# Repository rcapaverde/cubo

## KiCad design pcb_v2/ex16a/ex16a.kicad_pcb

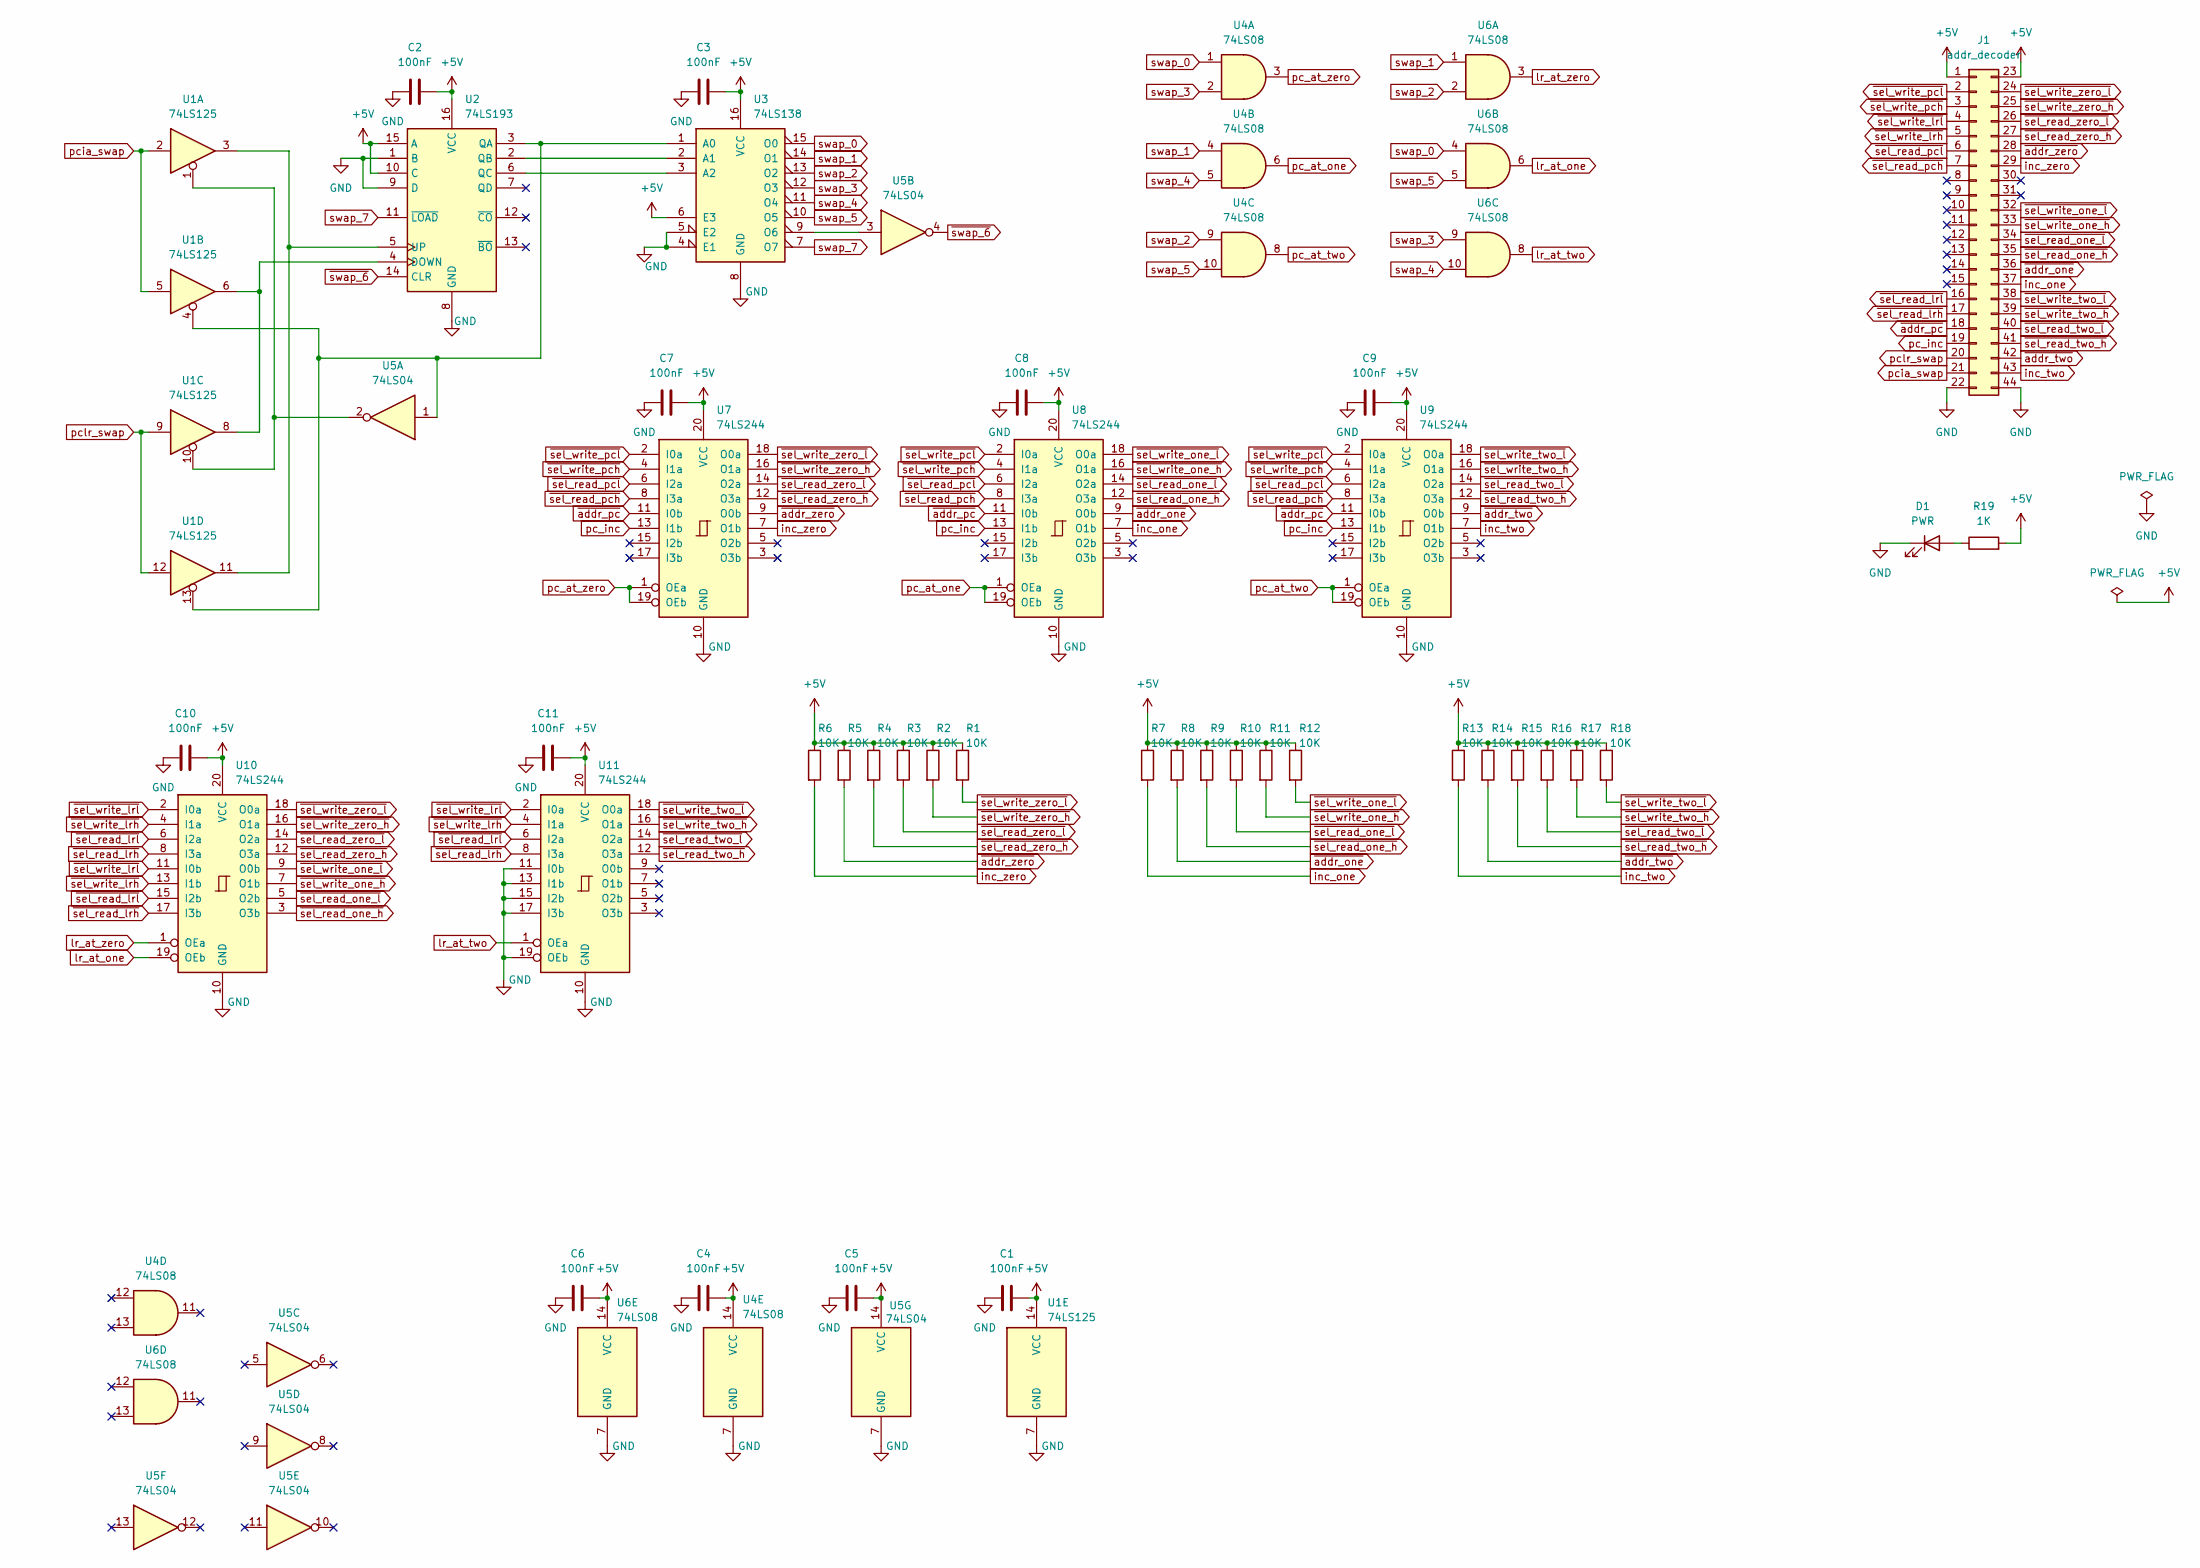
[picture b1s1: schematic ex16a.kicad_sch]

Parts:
C1, C2, C3, C4, C5, C6, C7, C8, C9, C10, C11: 100nF; C_Disc_D5.1mm_W3.2mm_P5.00mm
D1: PWR; LED_D5.0mm
J1: addr_decoder; edge-connector-44
R1, R2, R3, R4, R5, R6, R7, R8, R9, R10, R11, R12, R13, R14, R15, R16, R17, R18: 10K; R_Axial_DIN0207_L6.3mm_D2.5mm_P7.62mm_Horizontal
R19: 1K; R_Axial_DIN0207_L6.3mm_D2.5mm_P7.62mm_Horizontal
U1: 74LS125; DIP-14_W7.62mm
U2: 74LS193; DIP-16_W7.62mm
U3: 74LS138; DIP-16_W7.62mm
U4, U6: 74LS08; DIP-14_W7.62mm
U5: 74LS04; DIP-14_W7.62mm
U7, U8, U9, U10, U11: 74LS244; DIP-20_W7.62mm

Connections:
+5V: C1.2, C2.2, C3.2, C4.2, C5.2, C6.2, C7.2, C8.2, C9.2, C10.2, C11.2, J1.1, J1.23, R1.1, R2.1, R3.1, R4.1, R5.1, R6.1, R7.1, R8.1, R9.1, R10.1, R11.1, R12.1, R13.1, R14.1, R15.1, R16.1, R17.1, R18.1, R19.2, U1.14 (VCC), U2.10 (C), U2.15 (A), U2.16 (VCC), U3.6 (E3), U3.16 (VCC), U4.14 (VCC), U5.14 (VCC), U6.14 (VCC), U7.20 (VCC), U8.20 (VCC), U9.20 (VCC), U10.20 (VCC), U11.20 (VCC)
GND: C1.1, C2.1, C3.1, C4.1, C5.1, C6.1, C7.1, C8.1, C9.1, C10.1, C11.1, D1.1 (K), J1.22, J1.44, U1.7 (GND), U2.1 (B), U2.8 (GND), U2.9 (D), U3.4 (E1), U3.5 (E2), U3.8 (GND), U4.7 (GND), U5.7 (GND), U6.7 (GND), U7.10 (GND), U8.10 (GND), U9.10 (GND), U10.10 (GND), U11.10 (GND), U11.11 (I0b), U11.13 (I1b), U11.15 (I2b), U11.17 (I3b), U11.19 (OEb)
unnamed: D1.2 (A), R19.1
unnamed: U1.1, U1.10, U5.2
unnamed: U1.6, U1.8, U2.4 (DOWN)
unnamed: U1.4, U1.13, U2.3 (QA), U3.1 (A0), U5.1
unnamed: U2.2 (QB), U3.2 (A1)
unnamed: U2.6 (QC), U3.3 (A2)
unnamed: U1.3, U1.11, U2.5 (UP)
unnamed: U3.9 (O6), U5.3
inc_one: J1.37, R7.2, U8.7 (O1b)
inc_two: J1.43, R13.2, U9.7 (O1b)
inc_zero: J1.29, R6.2, U7.7 (O1b)
lr_at_one: U6.6, U10.19 (OEb)
lr_at_two: U6.8, U11.1 (OEa)
lr_at_zero: U6.3, U10.1 (OEa)
pc_at_one: U4.6, U8.1 (OEa), U8.19 (OEb)
pc_at_two: U4.8, U9.1 (OEa), U9.19 (OEb)
pc_at_zero: U4.3, U7.1 (OEa), U7.19 (OEb)
pc_inc: J1.19, U7.13 (I1b), U8.13 (I1b), U9.13 (I1b)
pcia_swap: J1.21, U1.2, U1.5
pclr_swap: J1.20, U1.9, U1.12
swap_0: U3.15 (O0), U4.1, U6.4
swap_1: U3.14 (O1), U4.4, U6.1
swap_2: U3.13 (O2), U4.9, U6.2
swap_3: U3.12 (O3), U4.2, U6.9
swap_4: U3.11 (O4), U4.5, U6.10
swap_5: U3.10 (O5), U4.10, U6.5
swap_7: U2.11 (~LOAD), U3.7 (O7)
~addr_one: J1.36, R8.2, U8.9 (O0b)
~addr_pc: J1.18, U7.11 (I0b), U8.11 (I0b), U9.11 (I0b)
~addr_two: J1.42, R14.2, U9.9 (O0b)
~addr_zero: J1.28, R5.2, U7.9 (O0b)
~sel_read_lrh: J1.17, U10.8 (I3a), U10.17 (I3b), U11.8 (I3a)
~sel_read_lrl: J1.16, U10.6 (I2a), U10.15 (I2b), U11.6 (I2a)
~sel_read_one_h: J1.35, R9.2, U8.12 (O3a), U10.3 (O3b)
~sel_read_one_l: J1.34, R10.2, U8.14 (O2a), U10.5 (O2b)
~sel_read_pch: J1.7, U7.8 (I3a), U8.8 (I3a), U9.8 (I3a)
~sel_read_pcl: J1.6, U7.6 (I2a), U8.6 (I2a), U9.6 (I2a)
~sel_read_two_h: J1.41, R15.2, U9.12 (O3a), U11.12 (O3a)
~sel_read_two_l: J1.40, R16.2, U9.14 (O2a), U11.14 (O2a)
~sel_read_zero_h: J1.27, R4.2, U7.12 (O3a), U10.12 (O3a)
~sel_read_zero_l: J1.26, R3.2, U7.14 (O2a), U10.14 (O2a)
~sel_write_lrh: J1.5, U10.4 (I1a), U10.13 (I1b), U11.4 (I1a)
~sel_write_lrl: J1.4, U10.2 (I0a), U10.11 (I0b), U11.2 (I0a)
~sel_write_one_h: J1.33, R11.2, U8.16 (O1a), U10.7 (O1b)
~sel_write_one_l: J1.32, R12.2, U8.18 (O0a), U10.9 (O0b)
~sel_write_pch: J1.3, U7.4 (I1a), U8.4 (I1a), U9.4 (I1a)
~sel_write_pcl: J1.2, U7.2 (I0a), U8.2 (I0a), U9.2 (I0a)
~sel_write_two_h: J1.39, R17.2, U9.16 (O1a), U11.16 (O1a)
~sel_write_two_l: J1.38, R18.2, U9.18 (O0a), U11.18 (O0a)
~sel_write_zero_h: J1.25, R2.2, U7.16 (O1a), U10.16 (O1a)
~sel_write_zero_l: J1.24, R1.2, U7.18 (O0a), U10.18 (O0a)
~swap_6: U2.14 (CLR), U5.4

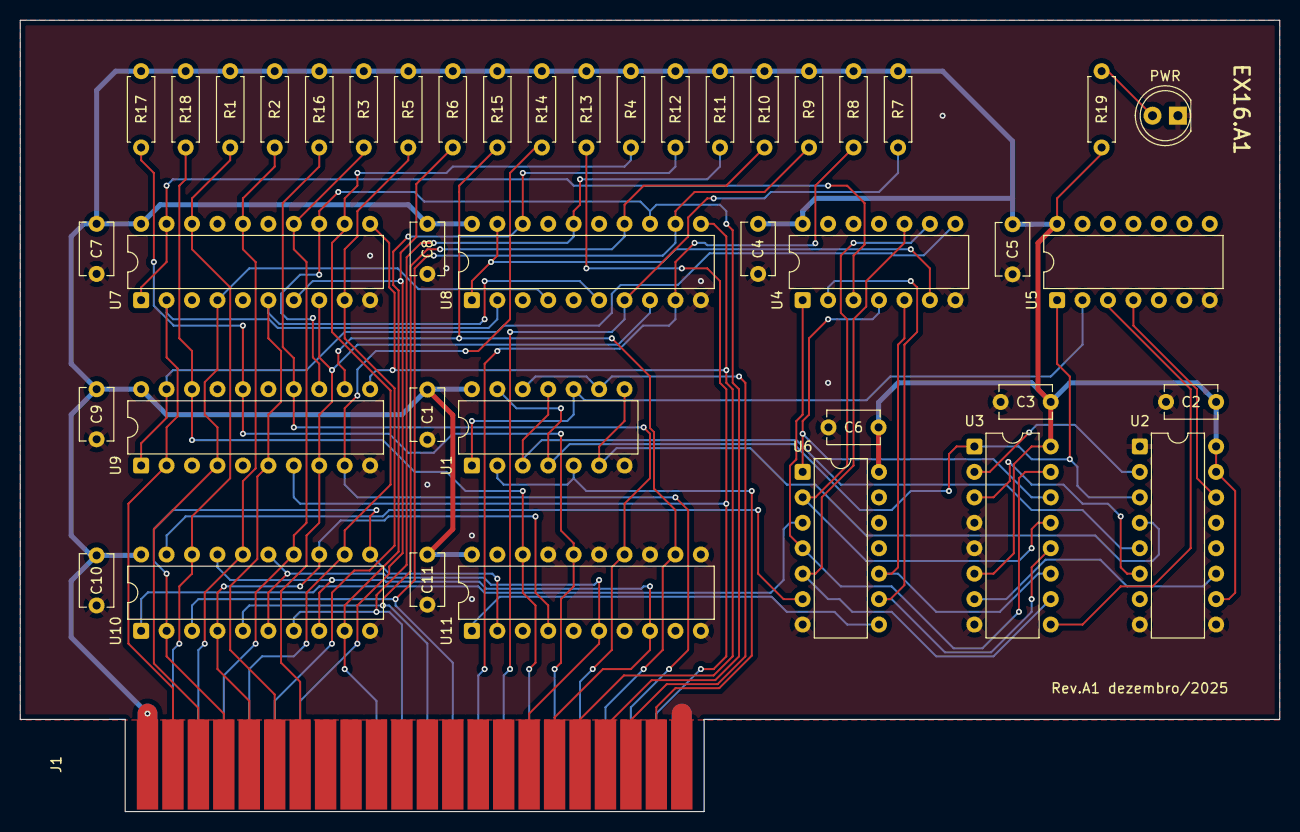
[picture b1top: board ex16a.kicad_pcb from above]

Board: 2 copper layers, 125.7 x 79.0 mm, 43 parts (0 on the bottom side), 54 nets.

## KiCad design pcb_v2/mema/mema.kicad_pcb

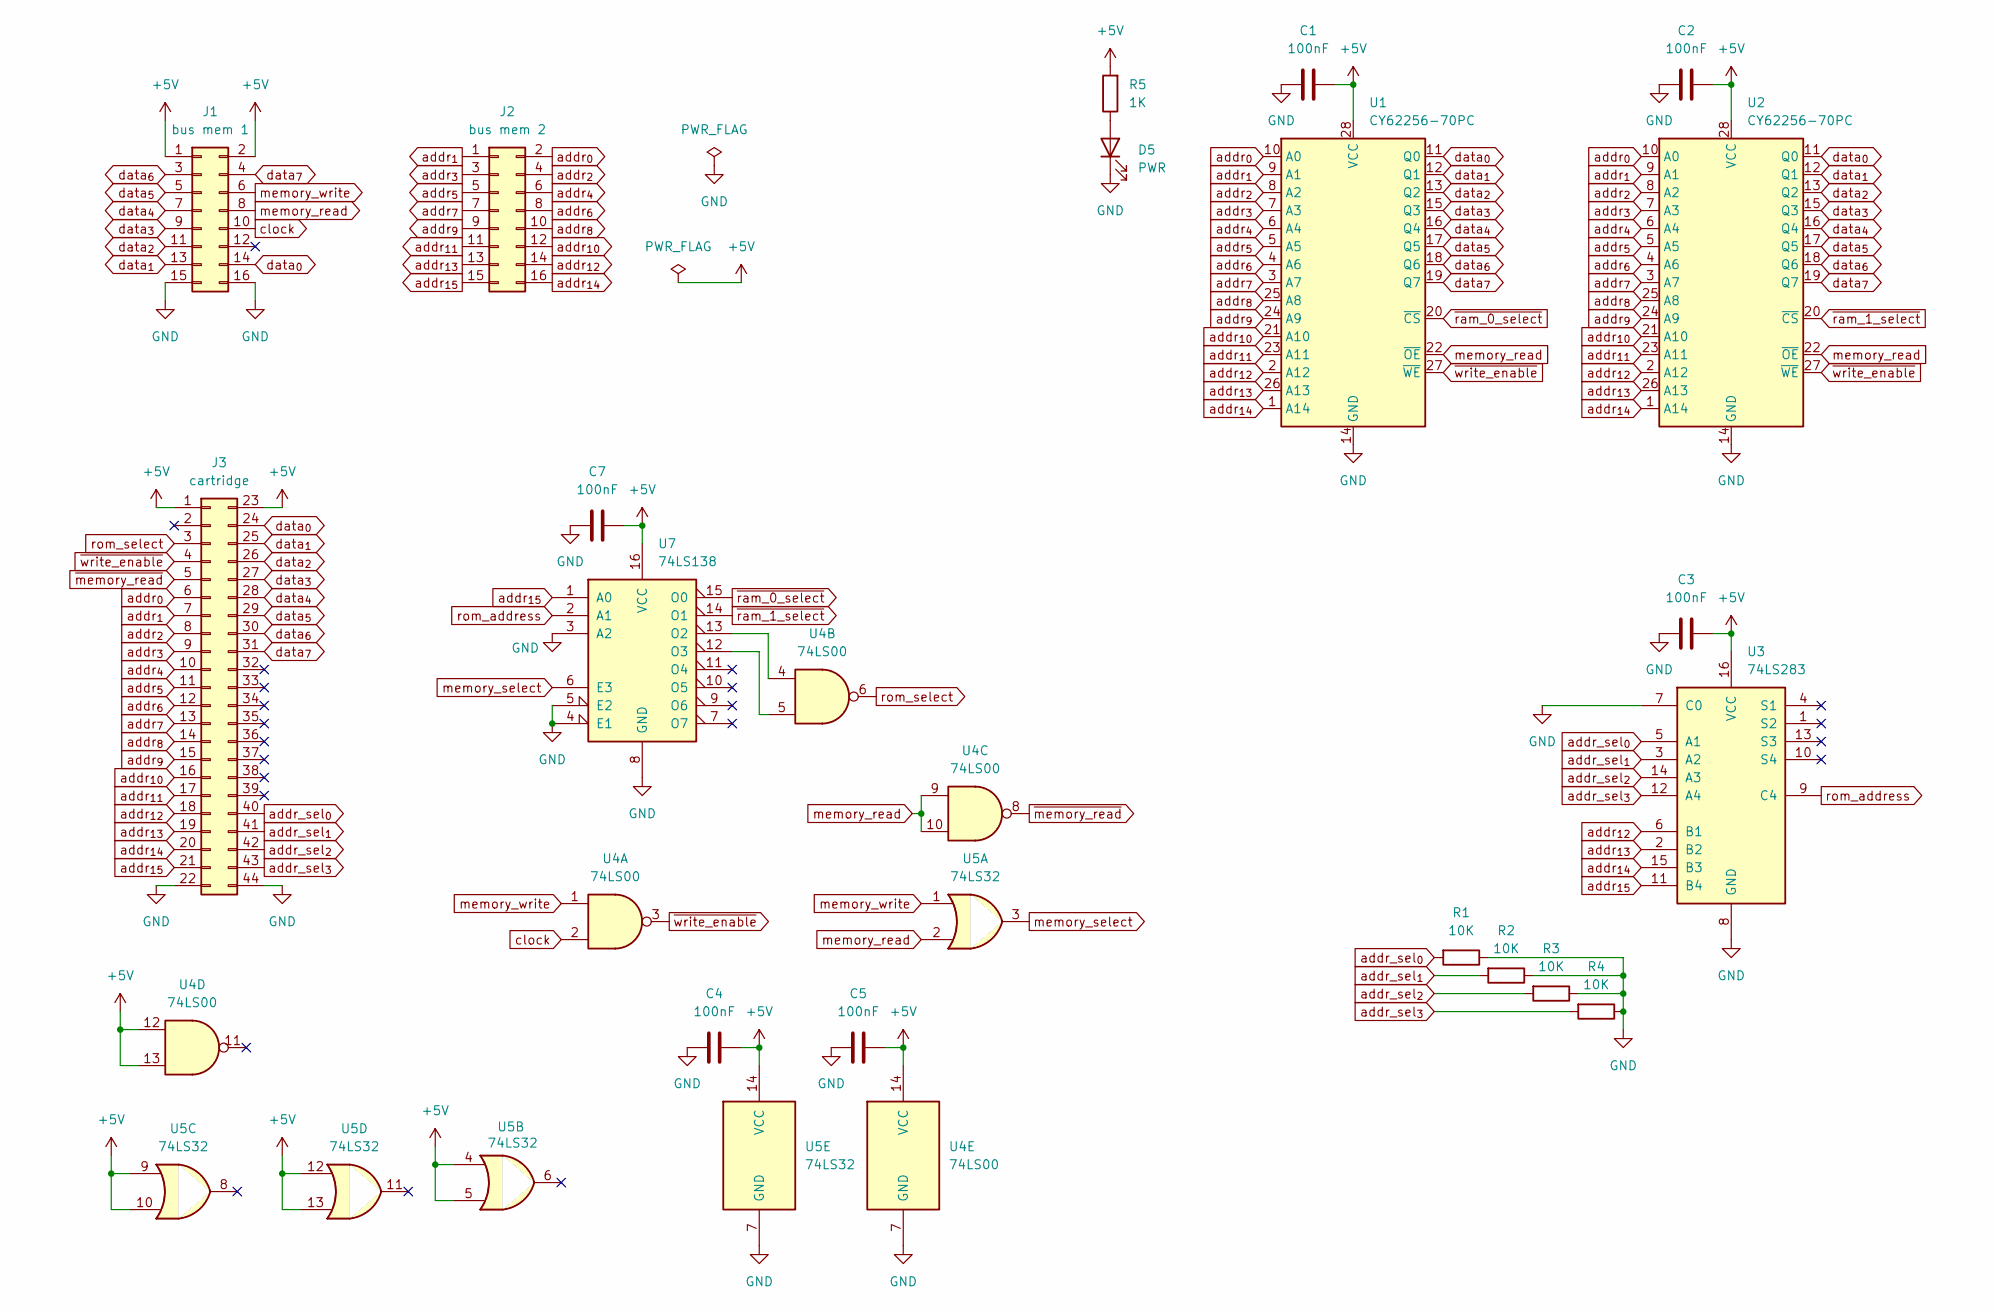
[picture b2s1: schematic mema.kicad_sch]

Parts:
C1, C2, C3, C4, C5, C7: 100nF; C_Disc_D5.1mm_W3.2mm_P5.00mm
D5: PWR; LED_D5.0mm
J1: bus mem 1; PinHeader_2x08_P2.54mm_Vertical
J2: bus mem 2; PinHeader_2x08_P2.54mm_Vertical
J3: cartridge; male-edge-connector-44
R1, R2, R3, R4: 10K; R_Axial_DIN0207_L6.3mm_D2.5mm_P7.62mm_Horizontal
R5: 1K; R_Axial_DIN0207_L6.3mm_D2.5mm_P7.62mm_Horizontal
U1, U2: CY62256-70PC; DIP-28_W15.24mm
U3: 74LS283; DIP-16_W7.62mm
U4: 74LS00; DIP-14_W7.62mm
U5: 74LS32; DIP-14_W7.62mm
U7: 74LS138; DIP-16_W7.62mm

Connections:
+5V: C1.2, C2.2, C3.2, C4.2, C5.2, C7.2, J1.1, J1.2, J3.1, J3.23, R5.2, U1.28 (VCC), U2.28 (VCC), U3.16 (VCC), U4.12, U4.13, U4.14 (VCC), U5.4, U5.5, U5.9, U5.10, U5.12, U5.13, U5.14 (VCC), U7.16 (VCC)
GND: C1.1, C2.1, C3.1, C4.1, C5.1, C7.1, D5.1 (K), J1.15, J1.16, J3.22, J3.44, R1.1, R2.1, R3.1, R4.1, U1.14 (GND), U2.14 (GND), U3.7 (C0), U3.8 (GND), U4.7 (GND), U5.7 (GND), U7.3 (A2), U7.4 (E1), U7.5 (E2), U7.8 (GND)
unnamed: D5.2 (A), R5.1
unnamed: U4.4, U7.13 (O2)
unnamed: U4.5, U7.12 (O3)
addr_sel_{0}: J3.40, R1.2, U3.5 (A1)
addr_sel_{1}: J3.41, R2.2, U3.3 (A2)
addr_sel_{2}: J3.42, R3.2, U3.14 (A3)
addr_sel_{3}: J3.43, R4.2, U3.12 (A4)
addr_{0}: J2.2, J3.6, U1.10 (A0), U2.10 (A0)
addr_{1}: J2.1, J3.7, U1.9 (A1), U2.9 (A1)
addr_{2}: J2.4, J3.8, U1.8 (A2), U2.8 (A2)
addr_{3}: J2.3, J3.9, U1.7 (A3), U2.7 (A3)
addr_{4}: J2.6, J3.10, U1.6 (A4), U2.6 (A4)
addr_{5}: J2.5, J3.11, U1.5 (A5), U2.5 (A5)
addr_{6}: J2.8, J3.12, U1.4 (A6), U2.4 (A6)
addr_{7}: J2.7, J3.13, U1.3 (A7), U2.3 (A7)
addr_{8}: J2.10, J3.14, U1.25 (A8), U2.25 (A8)
addr_{9}: J2.9, J3.15, U1.24 (A9), U2.24 (A9)
addr_{10}: J2.12, J3.16, U1.21 (A10), U2.21 (A10)
addr_{11}: J2.11, J3.17, U1.23 (A11), U2.23 (A11)
addr_{12}: J2.14, J3.18, U1.2 (A12), U2.2 (A12), U3.6 (B1)
addr_{13}: J2.13, J3.19, U1.26 (A13), U2.26 (A13), U3.2 (B2)
addr_{14}: J2.16, J3.20, U1.1 (A14), U2.1 (A14), U3.15 (B3)
addr_{15}: J2.15, J3.21, U3.11 (B4), U7.1 (A0)
clock: J1.10, U4.2
data_{0}: J1.14, J3.24, U1.11 (Q0), U2.11 (Q0)
data_{1}: J1.13, J3.25, U1.12 (Q1), U2.12 (Q1)
data_{2}: J1.11, J3.26, U1.13 (Q2), U2.13 (Q2)
data_{3}: J1.9, J3.27, U1.15 (Q3), U2.15 (Q3)
data_{4}: J1.7, J3.28, U1.16 (Q4), U2.16 (Q4)
data_{5}: J1.5, J3.29, U1.17 (Q5), U2.17 (Q5)
data_{6}: J1.3, J3.30, U1.18 (Q6), U2.18 (Q6)
data_{7}: J1.4, J3.31, U1.19 (Q7), U2.19 (Q7)
memory_read: J1.8, U1.22 (~OE), U2.22 (~OE), U4.9, U4.10, U5.2
memory_select: U5.3, U7.6 (E3)
memory_write: J1.6, U4.1, U5.1
rom_address: U3.9 (C4), U7.2 (A1)
rom_select: J3.3, U4.6
~memory_read: J3.5, U4.8
~ram_0_select: U1.20 (~CS), U7.15 (O0)
~ram_1_select: U2.20 (~CS), U7.14 (O1)
~write_enable: J3.4, U1.27 (~WE), U2.27 (~WE), U4.3

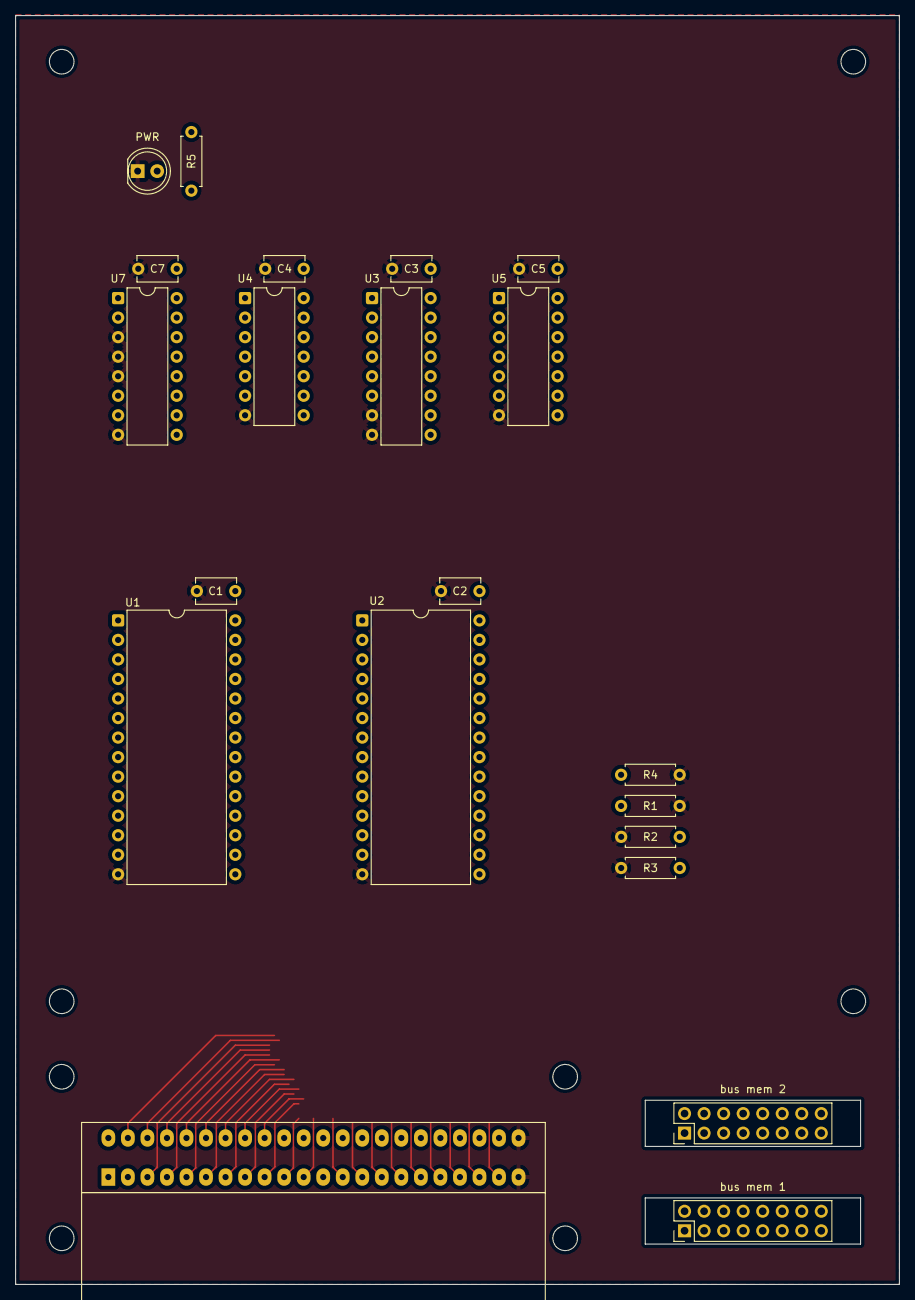
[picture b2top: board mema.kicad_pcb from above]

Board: 2 copper layers, 114.9 x 165.0 mm, 21 parts (0 on the bottom side), 43 nets.

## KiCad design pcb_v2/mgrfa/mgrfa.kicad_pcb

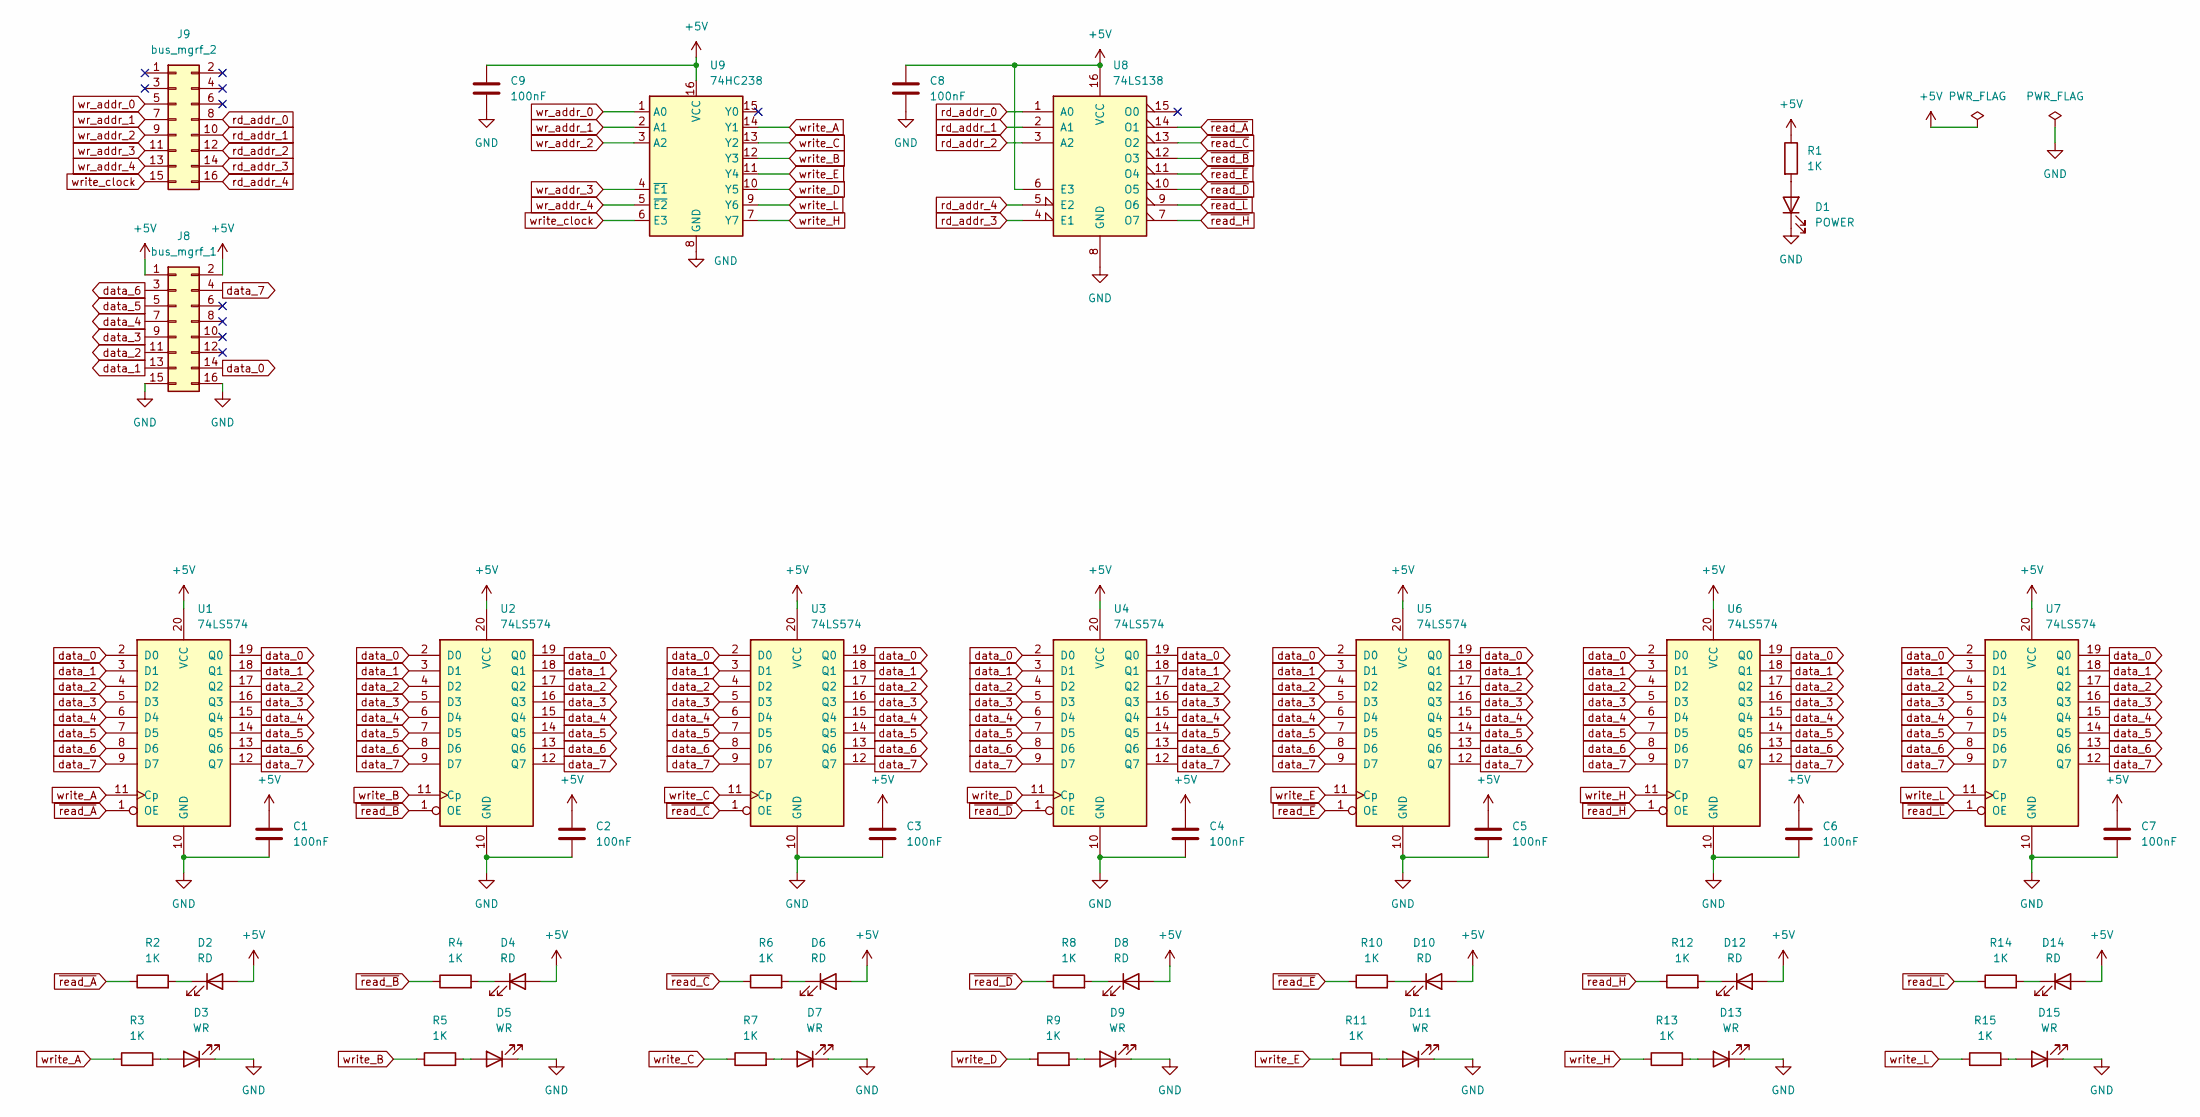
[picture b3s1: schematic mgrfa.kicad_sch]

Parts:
C1, C2, C3, C4, C5, C6, C7: 100nF; C_Disc_D5.1mm_W3.2mm_P5.00mm
C8, C9: 100nF; C_Disc_D4.7mm_W2.5mm_P5.00mm
D1: POWER; LED_D5.0mm
D2, D4, D6, D8, D10, D12, D14: RD; LED_D5.0mm
D3, D5, D7, D9, D11, D13, D15: WR; LED_D5.0mm
J8: bus_mgrf_1; PinHeader_2x08_P2.54mm_Vertical
J9: bus_mgrf_2; PinHeader_2x08_P2.54mm_Vertical
R1, R2, R3, R4, R5, R6, R7, R8, R9, R10, R11, R12, R13, R14, R15: 1K; R_Axial_DIN0207_L6.3mm_D2.5mm_P7.62mm_Horizontal
U1, U2, U3, U4, U5, U6, U7: 74LS574; DIP-20_W7.62mm
U8: 74LS138; DIP-16_W7.62mm
U9: 74HC238; DIP-16_W7.62mm

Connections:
+5V: C1.1, C2.1, C3.1, C4.1, C5.1, C6.1, C7.1, C8.1, C9.1, D2.2 (A), D4.2 (A), D6.2 (A), D8.2 (A), D10.2 (A), D12.2 (A), D14.2 (A), J8.1, J8.2, R1.1, U1.20 (VCC), U2.20 (VCC), U3.20 (VCC), U4.20 (VCC), U5.20 (VCC), U6.20 (VCC), U7.20 (VCC), U8.6 (E3), U8.16 (VCC), U9.16 (VCC)
GND: C1.2, C2.2, C3.2, C4.2, C5.2, C6.2, C7.2, C8.2, C9.2, D1.1 (K), D3.1 (K), D5.1 (K), D7.1 (K), D9.1 (K), D11.1 (K), D13.1 (K), D15.1 (K), J8.15, J8.16, U1.10 (GND), U2.10 (GND), U3.10 (GND), U4.10 (GND), U5.10 (GND), U6.10 (GND), U7.10 (GND), U8.8 (GND), U9.8 (GND)
unnamed: D1.2 (A), R1.2
unnamed: D2.1 (K), R2.2
unnamed: D3.2 (A), R3.2
unnamed: D4.1 (K), R4.2
unnamed: D5.2 (A), R5.2
unnamed: D6.1 (K), R6.2
unnamed: D7.2 (A), R7.2
unnamed: D8.1 (K), R8.2
unnamed: D9.2 (A), R9.2
unnamed: D10.1 (K), R10.2
unnamed: D11.2 (A), R11.2
unnamed: D12.1 (K), R12.2
unnamed: D13.2 (A), R13.2
unnamed: D14.1 (K), R14.2
unnamed: D15.2 (A), R15.2
data_0: J8.14, U1.2 (D0), U1.19 (Q0), U2.2 (D0), U2.19 (Q0), U3.2 (D0), U3.19 (Q0), U4.2 (D0), U4.19 (Q0), U5.2 (D0), U5.19 (Q0), U6.2 (D0), U6.19 (Q0), U7.2 (D0), U7.19 (Q0)
data_1: J8.13, U1.3 (D1), U1.18 (Q1), U2.3 (D1), U2.18 (Q1), U3.3 (D1), U3.18 (Q1), U4.3 (D1), U4.18 (Q1), U5.3 (D1), U5.18 (Q1), U6.3 (D1), U6.18 (Q1), U7.3 (D1), U7.18 (Q1)
data_2: J8.11, U1.4 (D2), U1.17 (Q2), U2.4 (D2), U2.17 (Q2), U3.4 (D2), U3.17 (Q2), U4.4 (D2), U4.17 (Q2), U5.4 (D2), U5.17 (Q2), U6.4 (D2), U6.17 (Q2), U7.4 (D2), U7.17 (Q2)
data_3: J8.9, U1.5 (D3), U1.16 (Q3), U2.5 (D3), U2.16 (Q3), U3.5 (D3), U3.16 (Q3), U4.5 (D3), U4.16 (Q3), U5.5 (D3), U5.16 (Q3), U6.5 (D3), U6.16 (Q3), U7.5 (D3), U7.16 (Q3)
data_4: J8.7, U1.6 (D4), U1.15 (Q4), U2.6 (D4), U2.15 (Q4), U3.6 (D4), U3.15 (Q4), U4.6 (D4), U4.15 (Q4), U5.6 (D4), U5.15 (Q4), U6.6 (D4), U6.15 (Q4), U7.6 (D4), U7.15 (Q4)
data_5: J8.5, U1.7 (D5), U1.14 (Q5), U2.7 (D5), U2.14 (Q5), U3.7 (D5), U3.14 (Q5), U4.7 (D5), U4.14 (Q5), U5.7 (D5), U5.14 (Q5), U6.7 (D5), U6.14 (Q5), U7.7 (D5), U7.14 (Q5)
data_6: J8.3, U1.8 (D6), U1.13 (Q6), U2.8 (D6), U2.13 (Q6), U3.8 (D6), U3.13 (Q6), U4.8 (D6), U4.13 (Q6), U5.8 (D6), U5.13 (Q6), U6.8 (D6), U6.13 (Q6), U7.8 (D6), U7.13 (Q6)
data_7: J8.4, U1.9 (D7), U1.12 (Q7), U2.9 (D7), U2.12 (Q7), U3.9 (D7), U3.12 (Q7), U4.9 (D7), U4.12 (Q7), U5.9 (D7), U5.12 (Q7), U6.9 (D7), U6.12 (Q7), U7.9 (D7), U7.12 (Q7)
rd_addr_0: J9.8, U8.1 (A0)
rd_addr_1: J9.10, U8.2 (A1)
rd_addr_2: J9.12, U8.3 (A2)
rd_addr_3: J9.14, U8.4 (E1)
rd_addr_4: J9.16, U8.5 (E2)
wr_addr_0: J9.5, U9.1 (A0)
wr_addr_1: J9.7, U9.2 (A1)
wr_addr_2: J9.9, U9.3 (A2)
wr_addr_3: J9.11, U9.4 (~E1)
wr_addr_4: J9.13, U9.5 (~E2)
write_A: R3.1, U1.11 (Cp), U9.14 (Y1)
write_B: R5.1, U2.11 (Cp), U9.12 (Y3)
write_C: R7.1, U3.11 (Cp), U9.13 (Y2)
write_D: R9.1, U4.11 (Cp), U9.10 (Y5)
write_E: R11.1, U5.11 (Cp), U9.11 (Y4)
write_H: R13.1, U6.11 (Cp), U9.7 (Y7)
write_L: R15.1, U7.11 (Cp), U9.9 (Y6)
write_clock: J9.15, U9.6 (E3)
~read_A: R2.1, U1.1 (OE), U8.14 (O1)
~read_B: R4.1, U2.1 (OE), U8.12 (O3)
~read_C: R6.1, U3.1 (OE), U8.13 (O2)
~read_D: R8.1, U4.1 (OE), U8.10 (O5)
~read_E: R10.1, U5.1 (OE), U8.11 (O4)
~read_H: R12.1, U6.1 (OE), U8.7 (O7)
~read_L: R14.1, U7.1 (OE), U8.9 (O6)

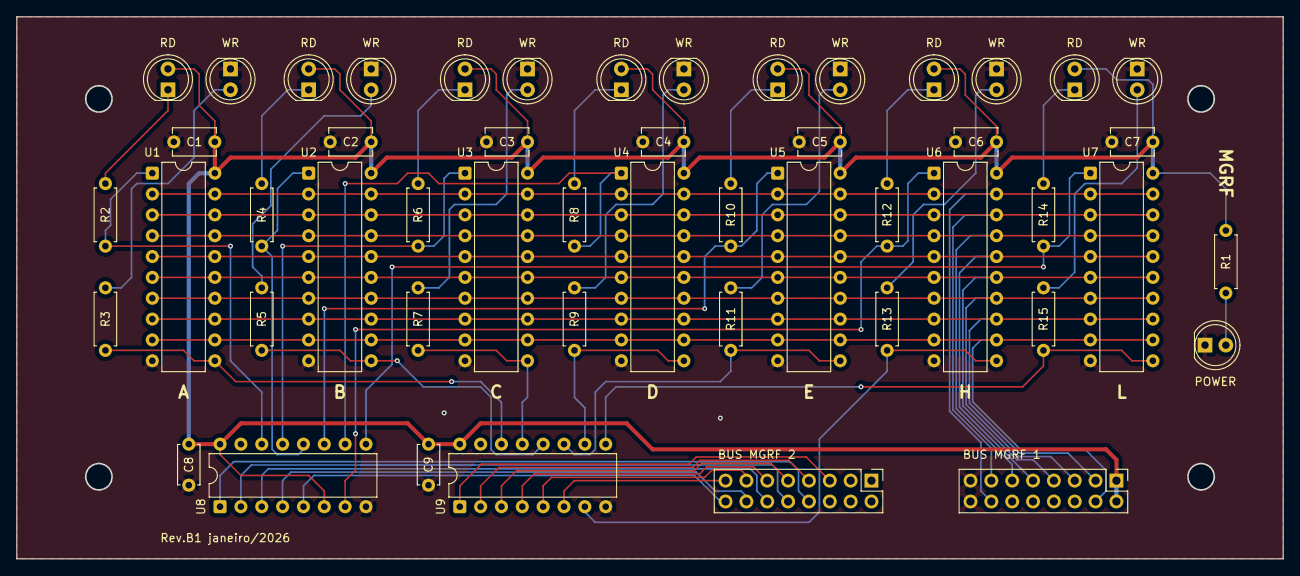
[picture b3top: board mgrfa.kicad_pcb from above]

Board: 2 copper layers, 154.3 x 66.0 mm, 50 parts (0 on the bottom side), 50 nets.

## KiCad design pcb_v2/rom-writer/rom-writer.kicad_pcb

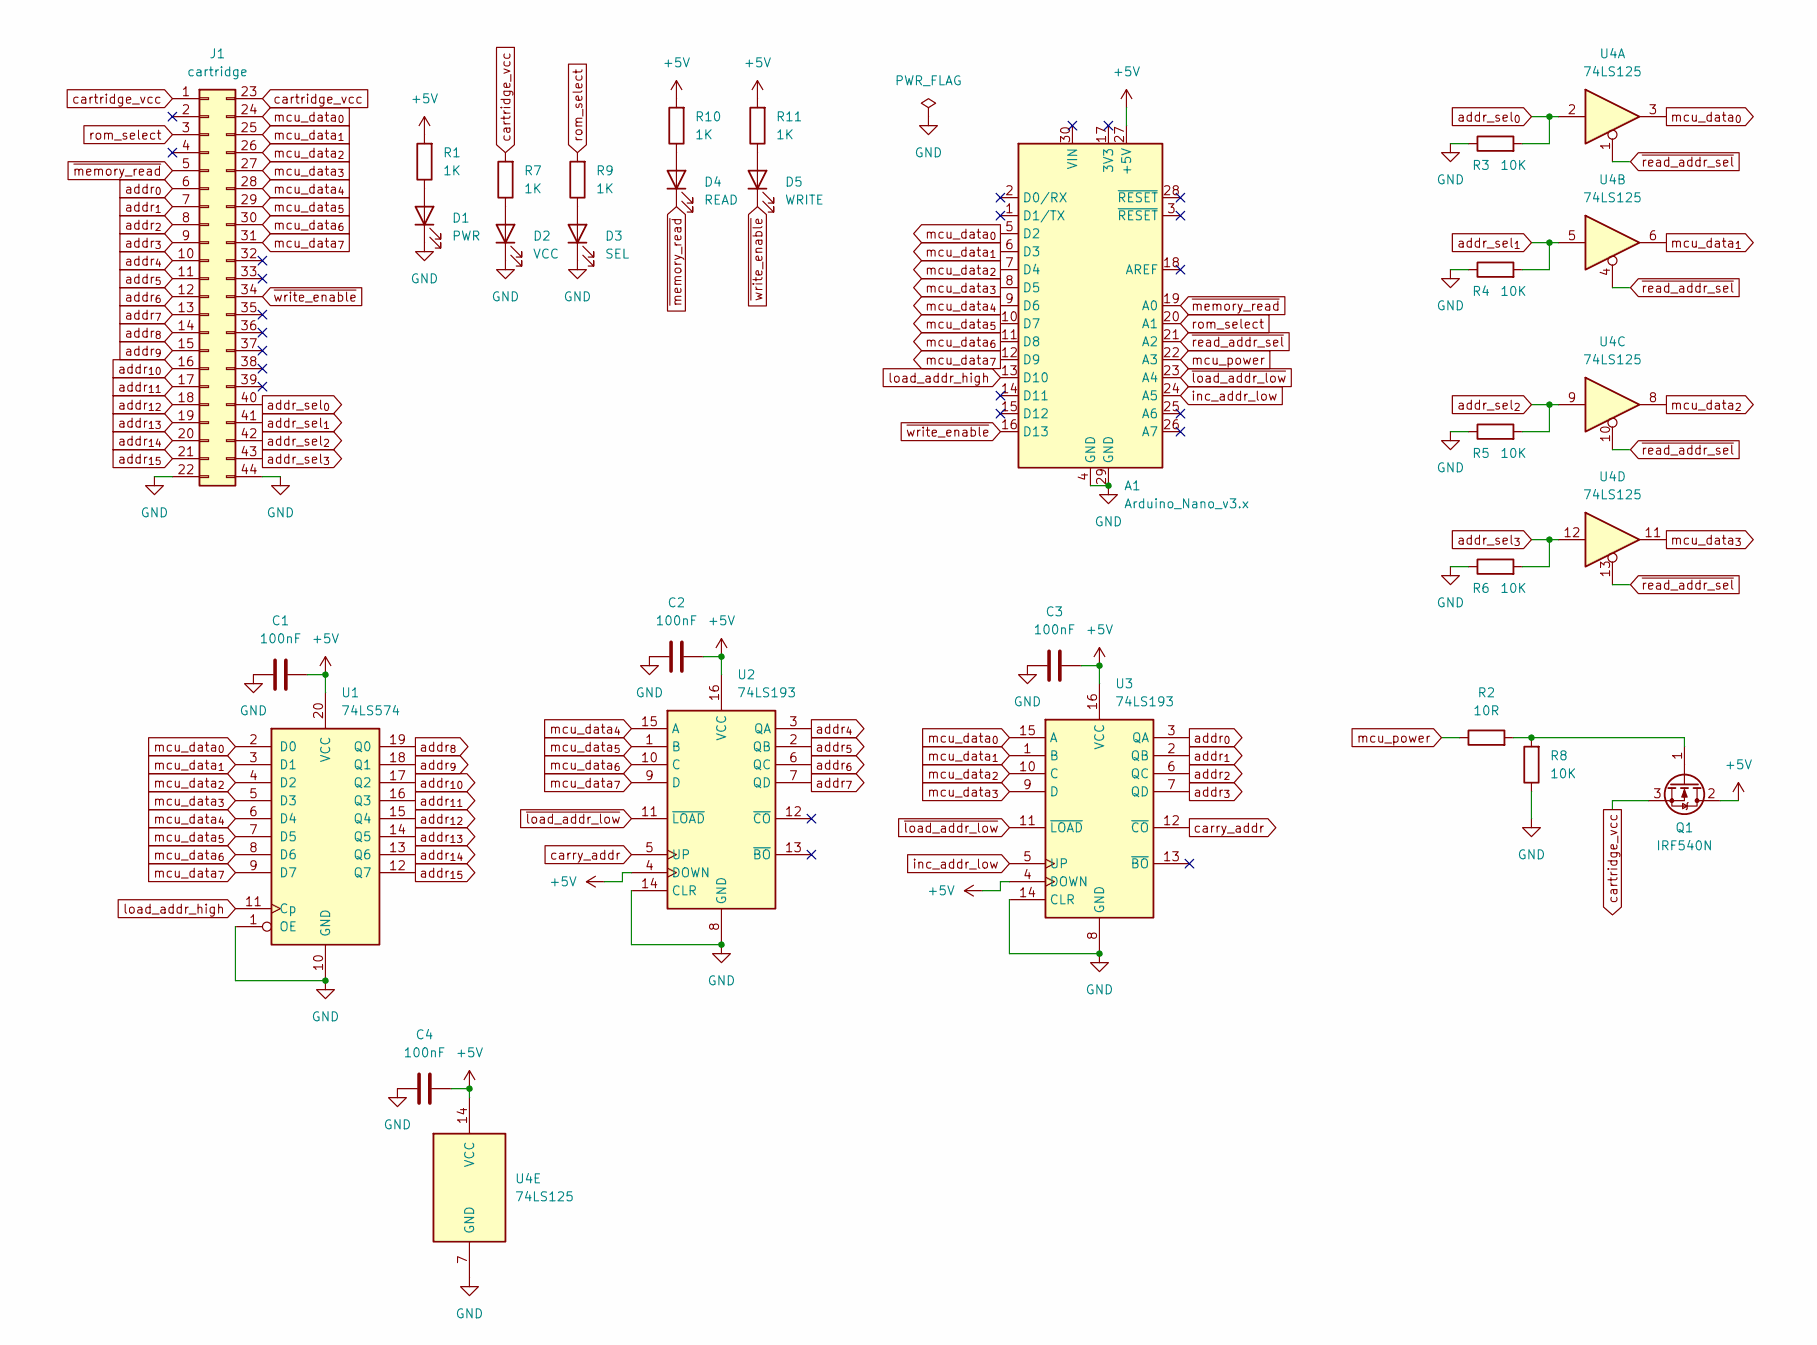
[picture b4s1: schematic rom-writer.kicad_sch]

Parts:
A1: Arduino_Nano_v3.x; Arduino_Nano
C1, C2, C3, C4: 100nF; C_Disc_D5.1mm_W3.2mm_P5.00mm
D1: PWR; LED_D5.0mm
D2: VCC; LED_D5.0mm
D3: SEL; LED_D5.0mm
D4: READ; LED_D5.0mm
D5: WRITE; LED_D5.0mm
J1: cartridge; male-edge-connector-44
Q1: IRF540N; TO-220-3_Vertical
R1, R7, R9, R10, R11: 1K; R_Axial_DIN0207_L6.3mm_D2.5mm_P7.62mm_Horizontal
R2: 10R; R_Axial_DIN0207_L6.3mm_D2.5mm_P7.62mm_Horizontal
R3, R4, R5, R6, R8: 10K; R_Axial_DIN0207_L6.3mm_D2.5mm_P7.62mm_Horizontal
U1: 74LS574; DIP-20_W7.62mm
U2, U3: 74LS193; DIP-16_W7.62mm
U4: 74LS125; DIP-14_W7.62mm

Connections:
+5V: A1.27 (+5V), C1.2, C2.2, C3.2, C4.2, Q1.2 (D), R1.2, R10.2, R11.2, U1.20 (VCC), U2.4 (DOWN), U2.16 (VCC), U3.4 (DOWN), U3.16 (VCC), U4.14 (VCC)
GND: A1.4 (GND), A1.29 (GND), C1.1, C2.1, C3.1, C4.1, D1.1 (K), D2.1 (K), D3.1 (K), J1.22, J1.44, R3.1, R4.1, R5.1, R6.1, R8.1, U1.1 (OE), U1.10 (GND), U2.8 (GND), U2.14 (CLR), U3.8 (GND), U3.14 (CLR), U4.7 (GND)
unnamed: D1.2 (A), R1.1
unnamed: D2.2 (A), R7.1
unnamed: D3.2 (A), R9.1
unnamed: D4.2 (A), R10.1
unnamed: D5.2 (A), R11.1
unnamed: Q1.1 (G), R2.2, R8.2
addr_sel_{0}: J1.40, R3.2, U4.2
addr_sel_{1}: J1.41, R4.2, U4.5
addr_sel_{2}: J1.42, R5.2, U4.9
addr_sel_{3}: J1.43, R6.2, U4.12
addr_{0}: J1.6, U3.3 (QA)
addr_{1}: J1.7, U3.2 (QB)
addr_{2}: J1.8, U3.6 (QC)
addr_{3}: J1.9, U3.7 (QD)
addr_{4}: J1.10, U2.3 (QA)
addr_{5}: J1.11, U2.2 (QB)
addr_{6}: J1.12, U2.6 (QC)
addr_{7}: J1.13, U2.7 (QD)
addr_{8}: J1.14, U1.19 (Q0)
addr_{9}: J1.15, U1.18 (Q1)
addr_{10}: J1.16, U1.17 (Q2)
addr_{11}: J1.17, U1.16 (Q3)
addr_{12}: J1.18, U1.15 (Q4)
addr_{13}: J1.19, U1.14 (Q5)
addr_{14}: J1.20, U1.13 (Q6)
addr_{15}: J1.21, U1.12 (Q7)
carry_addr: U2.5 (UP), U3.12 (~CO)
cartridge_vcc: J1.1, J1.23, Q1.3 (S), R7.2
inc_addr_low: A1.24 (A5), U3.5 (UP)
load_addr_high: A1.13 (D10), U1.11 (Cp)
mcu_data_{0}: A1.5 (D2), J1.24, U1.2 (D0), U3.15 (A), U4.3
mcu_data_{1}: A1.6 (D3), J1.25, U1.3 (D1), U3.1 (B), U4.6
mcu_data_{2}: A1.7 (D4), J1.26, U1.4 (D2), U3.10 (C), U4.8
mcu_data_{3}: A1.8 (D5), J1.27, U1.5 (D3), U3.9 (D), U4.11
mcu_data_{4}: A1.9 (D6), J1.28, U1.6 (D4), U2.15 (A)
mcu_data_{5}: A1.10 (D7), J1.29, U1.7 (D5), U2.1 (B)
mcu_data_{6}: A1.11 (D8), J1.30, U1.8 (D6), U2.10 (C)
mcu_data_{7}: A1.12 (D9), J1.31, U1.9 (D7), U2.9 (D)
mcu_power: A1.22 (A3), R2.1
rom_select: A1.20 (A1), J1.3, R9.2
~load_addr_low: A1.23 (A4), U2.11 (~LOAD), U3.11 (~LOAD)
~memory_read: A1.19 (A0), D4.1 (K), J1.5
~read_addr_sel: A1.21 (A2), U4.1, U4.4, U4.10, U4.13
~write_enable: A1.16 (D13), D5.1 (K), J1.34

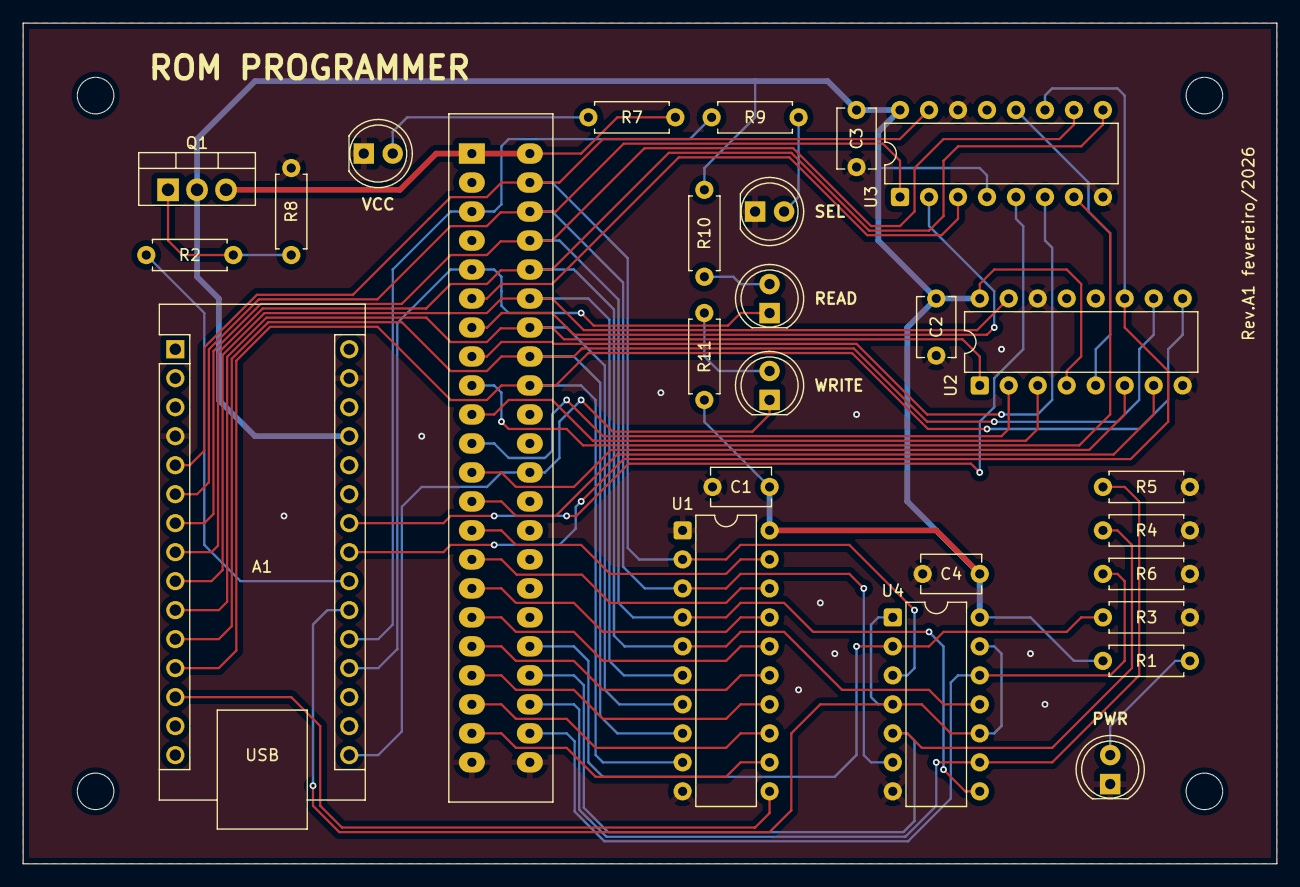
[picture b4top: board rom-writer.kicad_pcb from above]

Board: 2 copper layers, 109.9 x 73.7 mm, 27 parts (0 on the bottom side), 46 nets.
